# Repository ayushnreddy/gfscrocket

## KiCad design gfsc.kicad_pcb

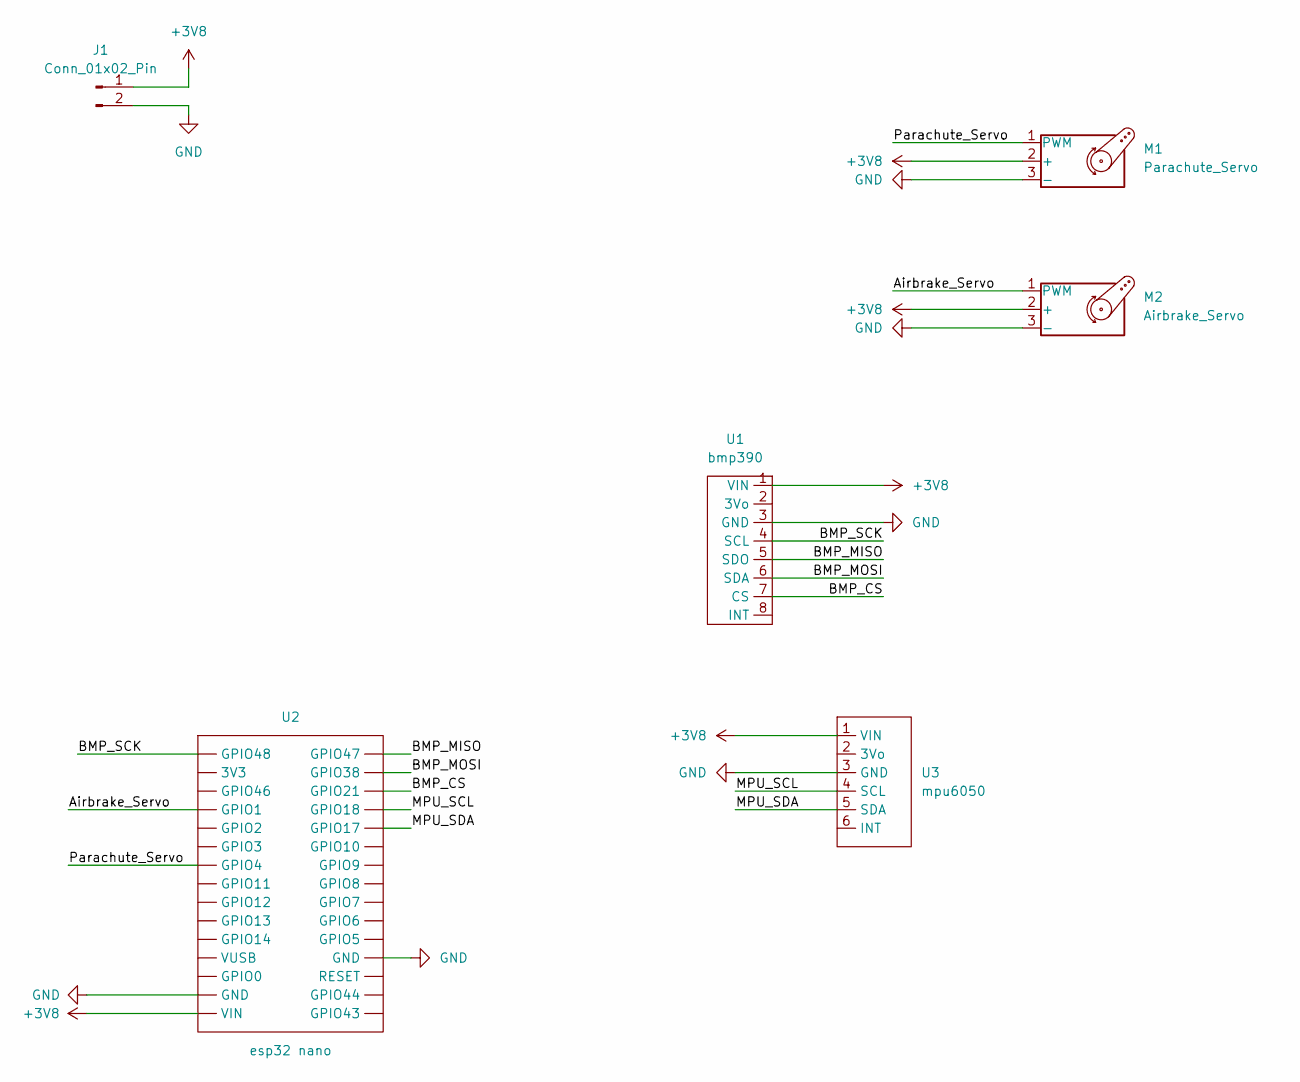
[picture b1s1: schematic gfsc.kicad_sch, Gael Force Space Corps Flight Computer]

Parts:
J1: Conn_01x02_Pin; PinHeader_1x02_P2.54mm_Vertical
M1: Parachute_Servo; PinHeader_1x03_P2.54mm_Vertical
M2: Airbrake_Servo; PinSocket_1x03_P2.54mm_Vertical
U1: bmp390
U2: esp32 nano
U3: mpu6050

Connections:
+3V8: J1.1, M1.2 (+), M2.2 (+), U1.1 (VIN), U2.15 (VIN), U3.1 (VIN)
/Airbrake_Servo: M2.1 (PWM), U2.4 (GPIO1)
/BMP_CS: U1.7 (CS), U2.18 (GPIO21)
/BMP_MISO: U1.5 (SDO), U2.16 (GPIO47)
/BMP_MOSI: U1.6 (SDA), U2.17 (GPIO38)
/BMP_SCK: U1.4 (SCL), U2.1 (GPIO48)
/MPU_SCL: U2.19 (GPIO18), U3.4 (SCL)
/MPU_SDA: U2.20 (GPIO17), U3.5 (SDA)
/Parachute_Servo: M1.1 (PWM), U2.7 (GPIO4)
GND: J1.2, M1.3 (-), M2.3 (-), U1.3 (GND), U2.14 (GND), U2.27 (GND), U3.3 (GND)

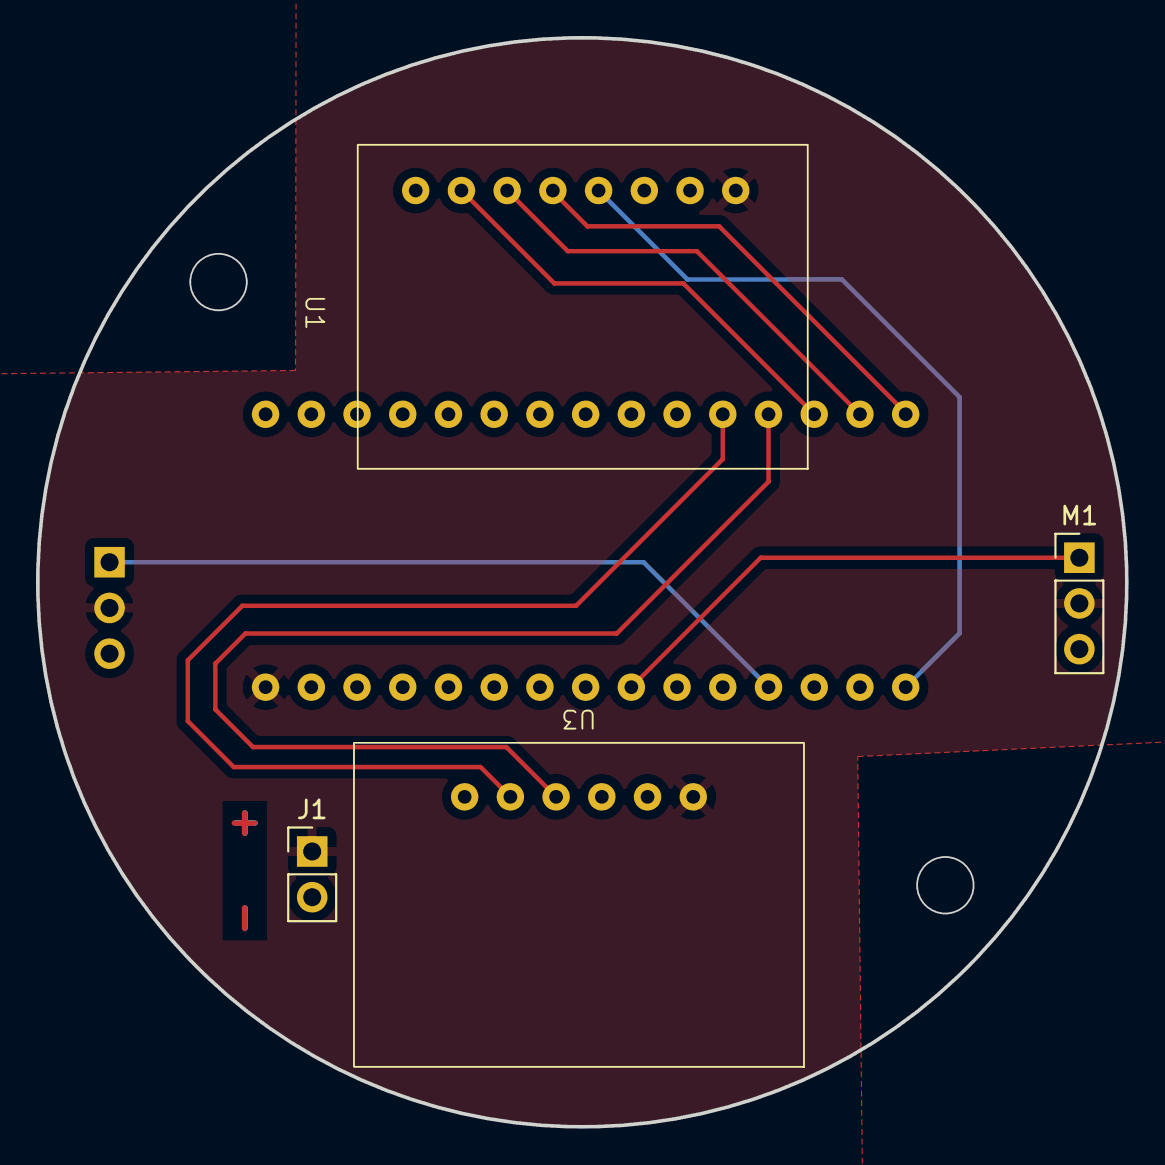
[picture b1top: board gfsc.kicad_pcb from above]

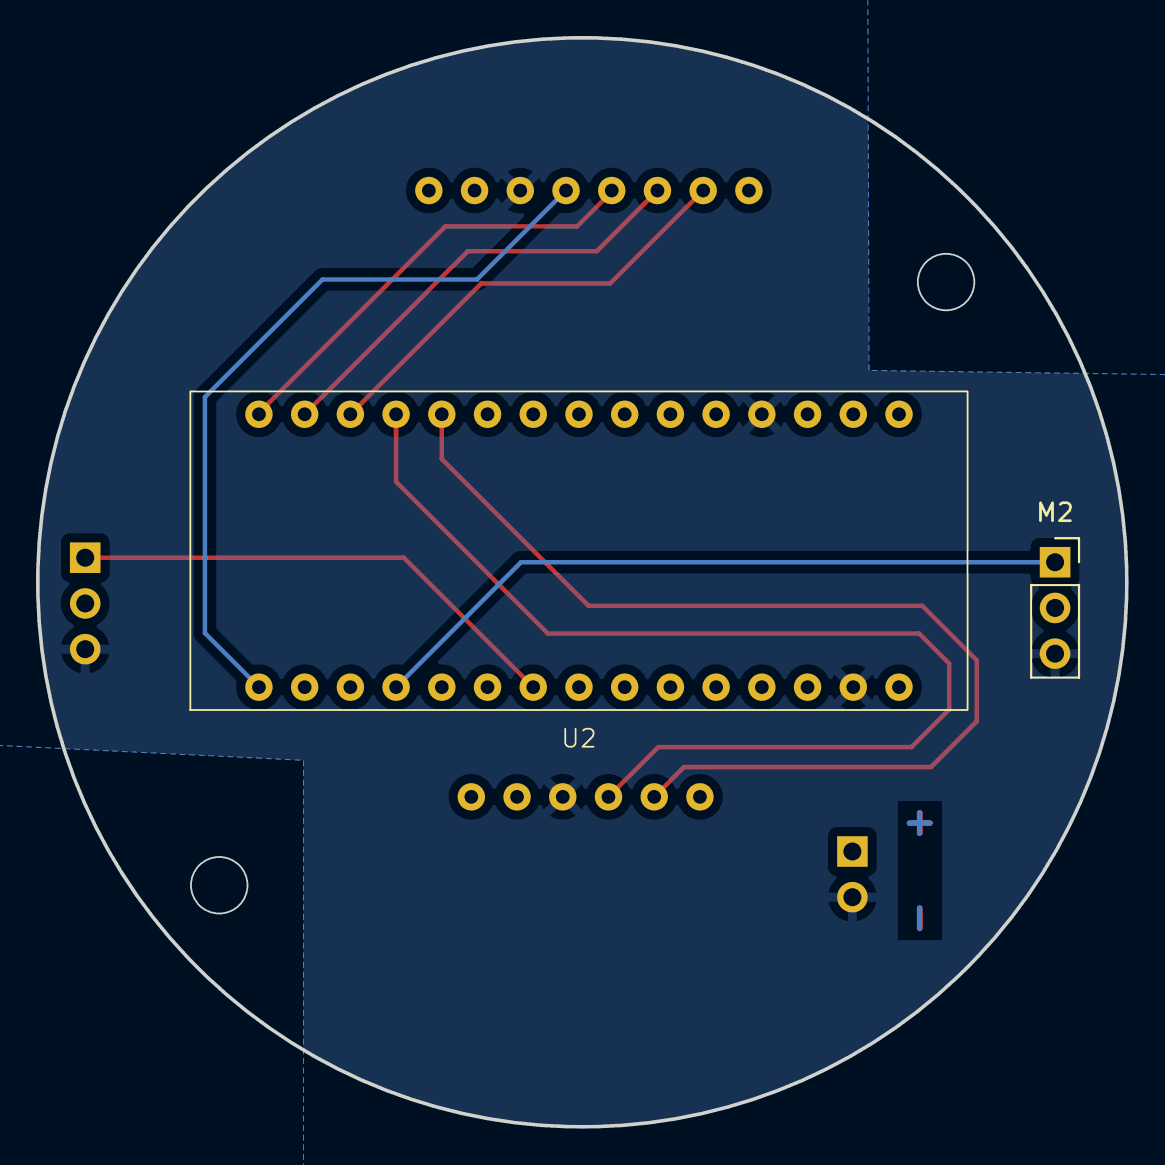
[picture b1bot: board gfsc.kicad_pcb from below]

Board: 2 copper layers, 60.5 x 60.5 mm, 6 parts (2 on the bottom side), 10 nets.
